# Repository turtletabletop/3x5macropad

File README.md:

# 3x5skymacropad

Hey everyone! This is my submission for [Hackpad V5](https://hackpad.hackclub.com/), a YSWS program in [Hack Club](https://hackclub.com/).

This macropad is a custom-built 3x5 ortholinear hot-swappable keyboard built off of the Seeed Studio XIAO RP2040 with a small OLED display. It uses Kailh Hot Swap Sockets, so it supports a variety of MX-style switches and uses QMK firmware. It's intended to mimic the Sky: Children of the Light digital music pad in-game.

## Features
- 15 programmable keys
- 128x32 OLED screen
- rad pcb silkscreen art
- QMK firmware
- a 3-degree tilt for more comfortable access to all the keys

## CAD + Case
### [Onshape link: <--- GO CLICK THIS!!!! It's a link to my CAD you can see online without downloading!!!](https://cad.onshape.com/documents/501449d828c00fab2d0b549b/w/615af9d6281a356a4f3616d7/e/420bb48ea47a66a72aa17e60?renderMode=0&uiState=6a62d55ca501a73d441c5f80)

I used Onshape for the CAD because I have previously used Onshape for FRC, and I thought Fusion360 was for nerds + online link sharing is fun!

Note that the mounting plate is intended to be fully transparent and made of acrylic/resin/any other clear material that can be used for a mounting plate. First time using Onshape for anything outside of robotics. Kept the case pretty simple. 

### Case Assembly:
The case is assembled by putting the heat set inserts in the top, and the bolts in the bottom.

## PCB
The entire PCB was made in KiCad! Note that I used [ScottoKeeb's KiCad library](https://github.com/joe-scotto/scottokeebs/tree/main/Extras/ScottoKicad) for the footprints and symbols because I was following [his guide](https://youtu.be/8WXpGTIbxlQ?). I had a lot of fun adding the silkscreen art for this; I just ripped a bunch of pictures from indie games I love + SkyCOTL. First time making a PCB! 

*without filled zones*

*with filled zones*

## PCB Schematic
dunno what to say here honestly just copied skottokeeb's guide for the most part

## Specifications
### Hardware used:
- Seeed Studio XIAO RP2040
- Kailh Hot Swap Sockets
- 128x32 OLED Screen

### Bill of Materials (BOM):
- 15x Cherry MX Switches
- 15x DSA Keycaps
- 1x Seeed Studio XIAO RP2040
- 4x M3x16mm SHCS Bolts
- 4x M3x5x4 Heatset inserts
- 1x 0.91" 128x32 OLED Display

### Inspiration:
This was mainly inspired by Sky: Children of the Light's in-game music pad. When you play an instrument in-game, a 3x5 tiled grid shows up where you can press each tile to play a musical note.

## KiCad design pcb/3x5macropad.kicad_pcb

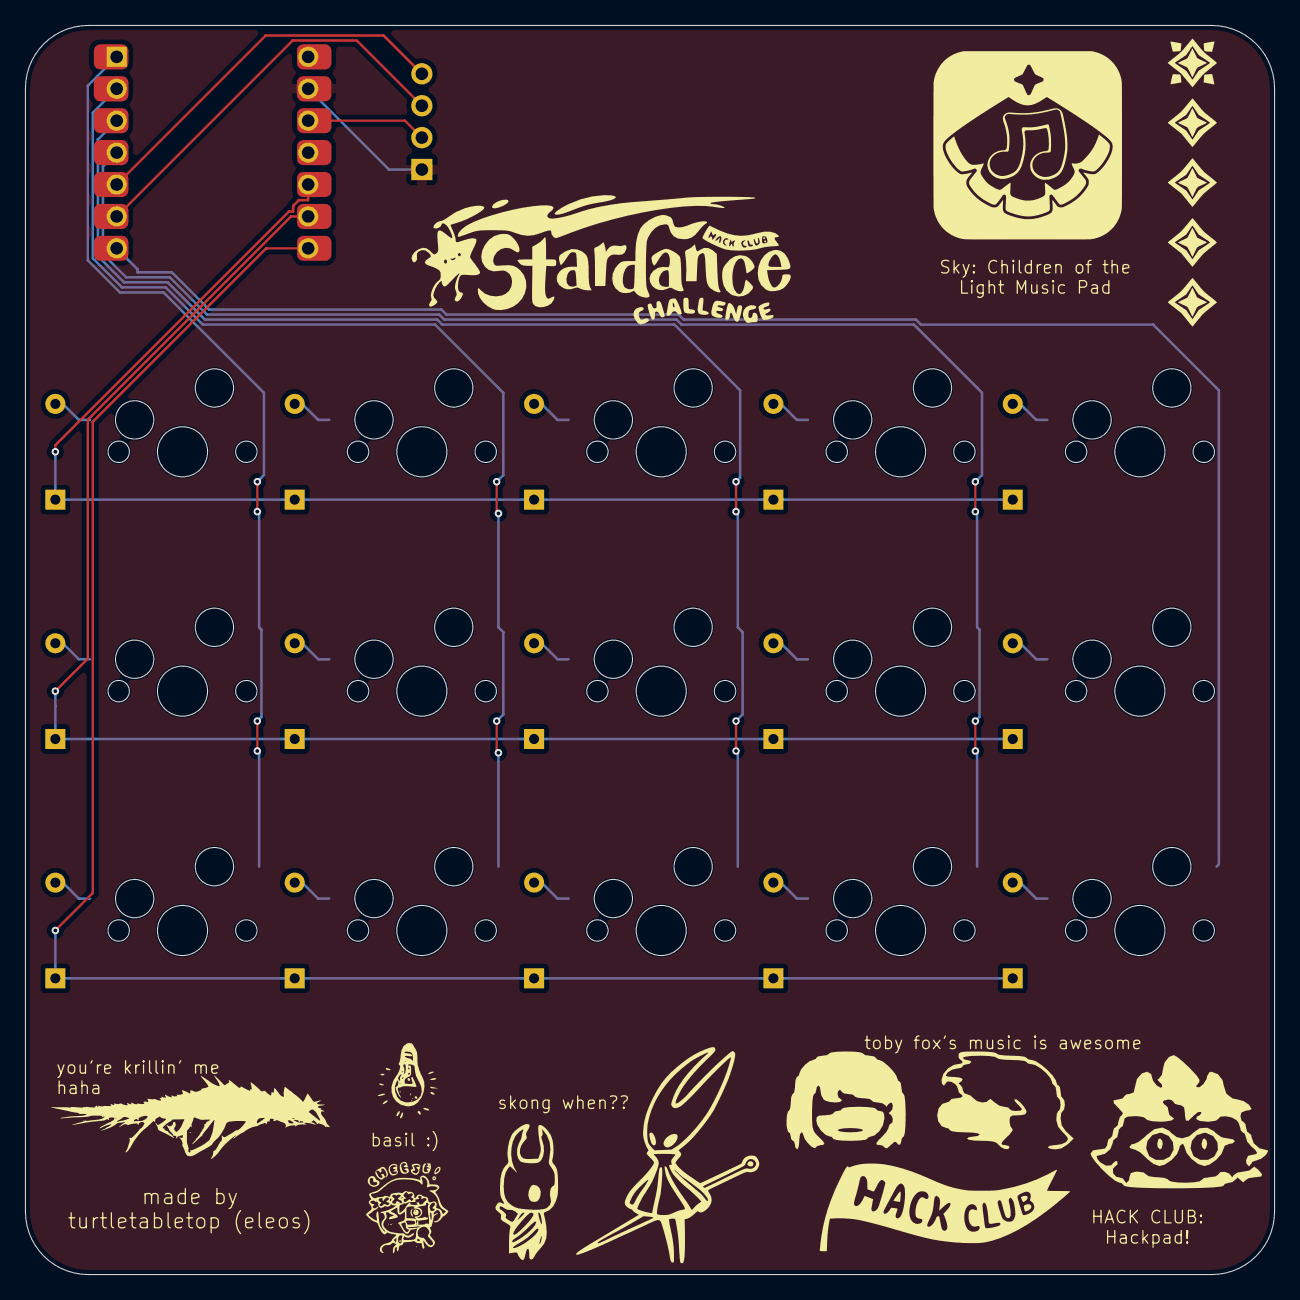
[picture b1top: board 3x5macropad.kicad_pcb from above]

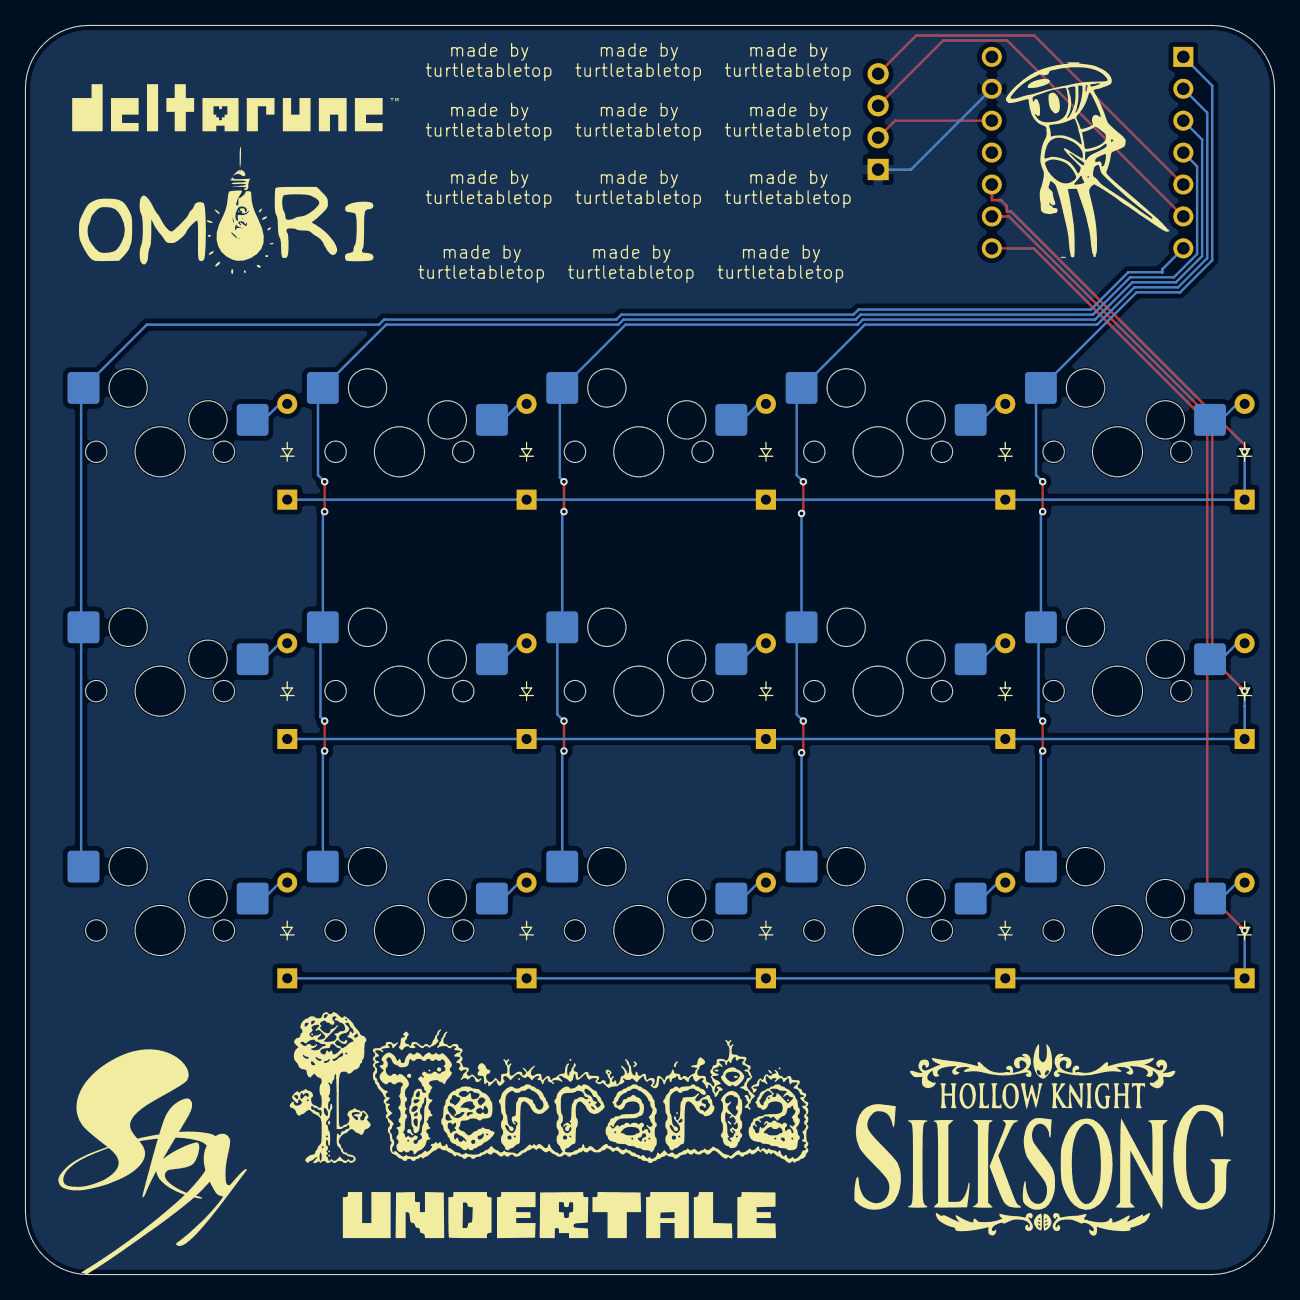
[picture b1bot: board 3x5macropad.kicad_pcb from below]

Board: 2 copper layers, 99.4 x 99.4 mm, 32 parts (30 on the bottom side), 27 nets.

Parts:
D1, D2, D3, D4, D5, D6, D7, D8, D9, D10, D11, D12, D13, D14, D15: Diode_DO-35
J1: OLED_128x32
S1, S2, S3, S4, S5, S6, S7, S8, S9, S10, S11, S12, S13, S14, S15: MX100H
U2: MCU_Seeed_XIAO_RP2040; Seeed_XIAO_RP2040

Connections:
/Column 0: S1.1, S6.1, S11.1, U2.7 (PB08_A6_D6_TX)
/Column 1: S2.1, S7.1, S12.1, U2.4 (PA11_A3_D3)
/Column 2: S3.1, S8.1, S13.1, U2.3 (PA10_A2_D2)
/Column 3: S4.1, S9.1, S14.1, U2.2 (PA4_A1_D1)
/Column 4: S5.1, S10.1, S15.1, U2.1 (PA02_A0_D0)
/Row 0: D1.1 (K), D2.1 (K), D3.1 (K), D4.1 (K), D5.1 (K), U2.10 (PA5_A9_D9_MISO)
/Row 1: D6.1 (K), D7.1 (K), D8.1 (K), D9.1 (K), D10.1 (K), U2.9 (PA7_A8_D8_SCK)
/Row 2: D11.1 (K), D12.1 (K), D13.1 (K), D14.1 (K), D15.1 (K), U2.8 (PB09_A7_D7_RX)
/oled 3.3v: J1.2 (VCC), U2.12 (3V3)
/oled ground: J1.1 (GND), U2.13 (GND)
/oled serial clock: J1.3 (SCL), U2.6 (PA9_A5_D5_SCL)
/oled serial data: J1.4 (SDA), U2.5 (PA8_A4_D4_SDA)
unnamed: D1.2 (A), S1.2
unnamed: D2.2 (A), S2.2
unnamed: D3.2 (A), S3.2
unnamed: D4.2 (A), S4.2
unnamed: D5.2 (A), S5.2
unnamed: D6.2 (A), S6.2
unnamed: D7.2 (A), S7.2
unnamed: D8.2 (A), S8.2
unnamed: D9.2 (A), S9.2
unnamed: D10.2 (A), S10.2
unnamed: D11.2 (A), S11.2
unnamed: D12.2 (A), S12.2
unnamed: D13.2 (A), S13.2
unnamed: D14.2 (A), S14.2
unnamed: D15.2 (A), S15.2
